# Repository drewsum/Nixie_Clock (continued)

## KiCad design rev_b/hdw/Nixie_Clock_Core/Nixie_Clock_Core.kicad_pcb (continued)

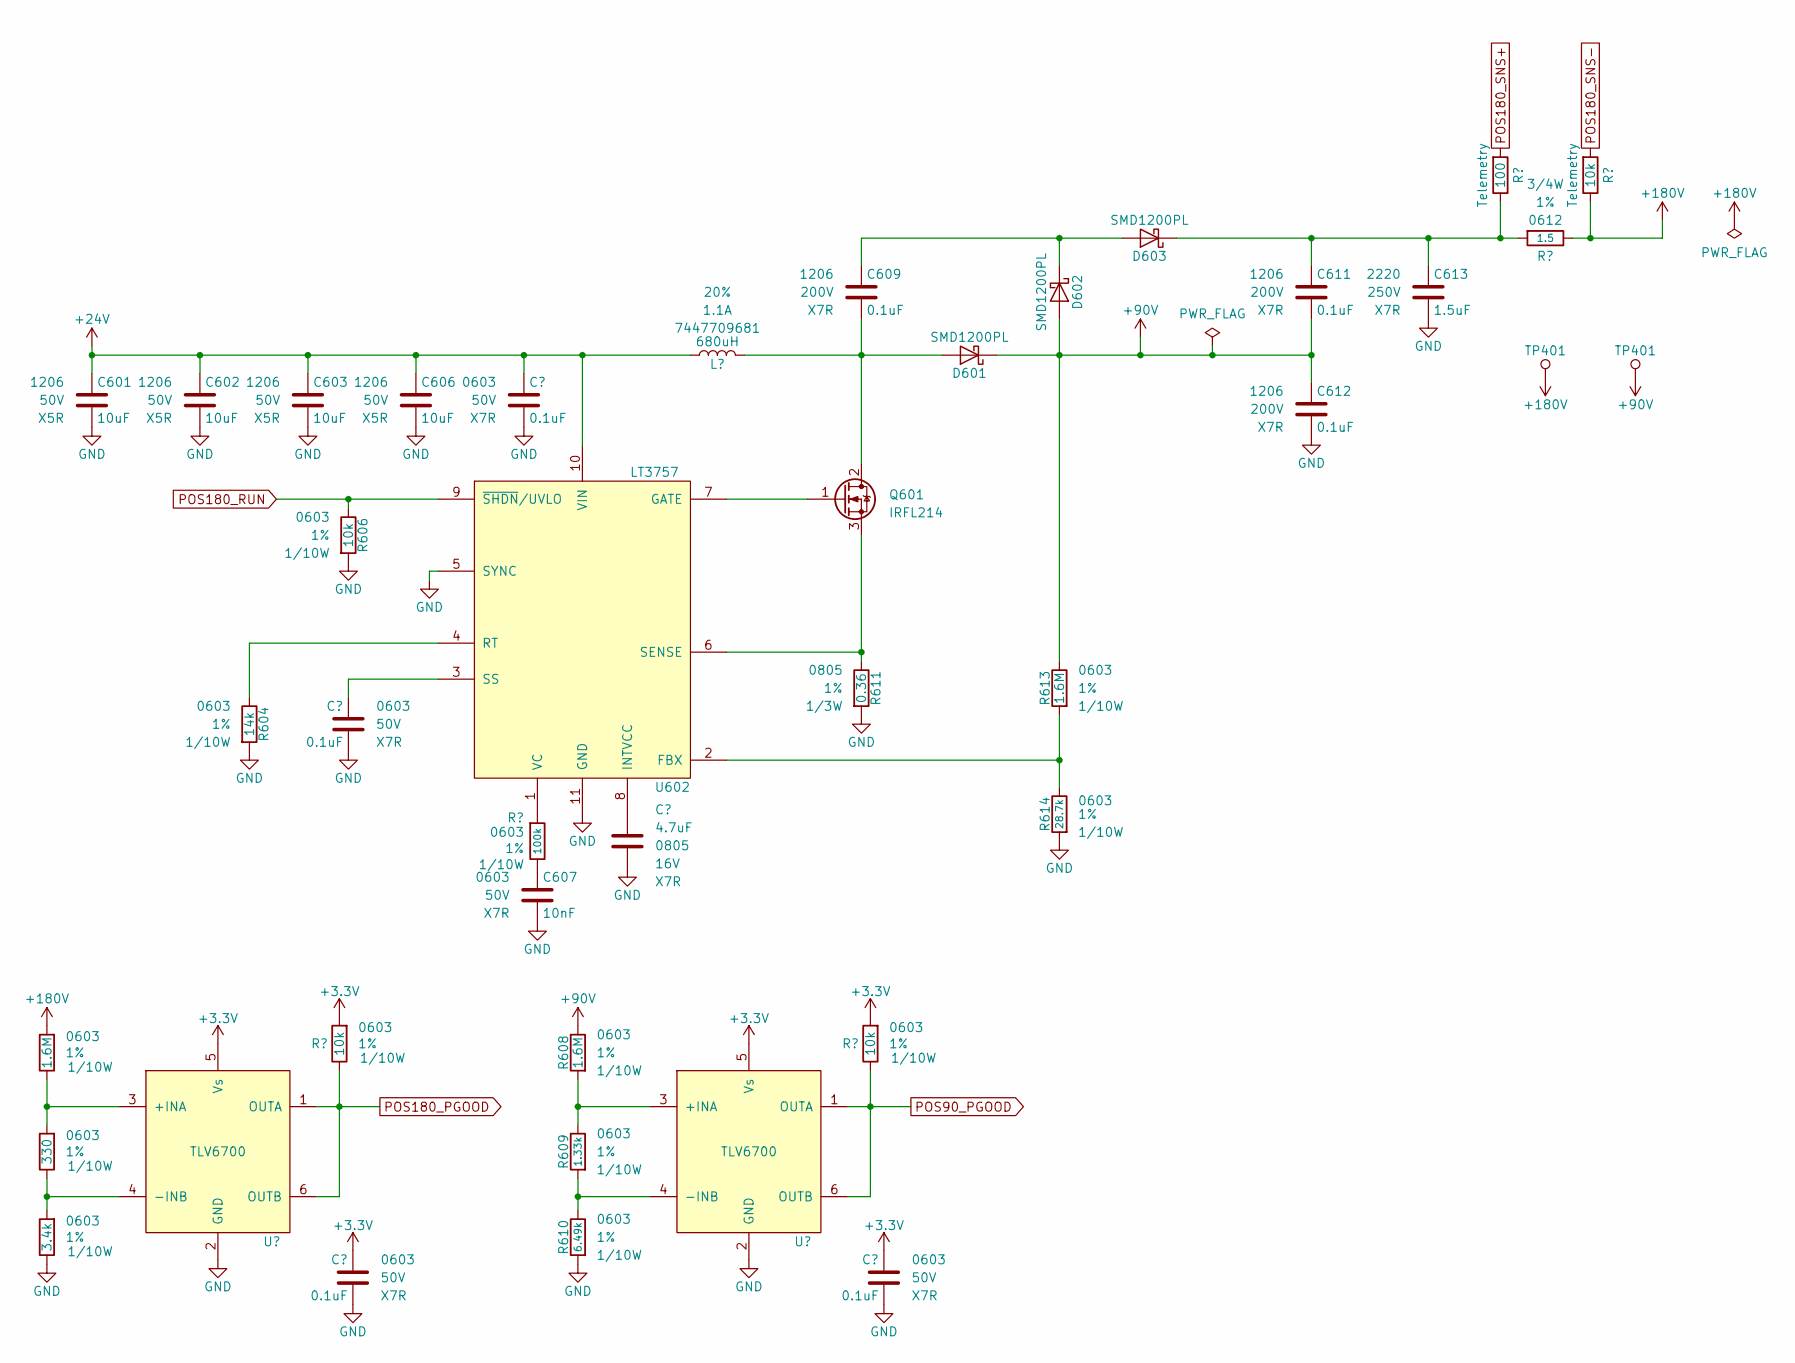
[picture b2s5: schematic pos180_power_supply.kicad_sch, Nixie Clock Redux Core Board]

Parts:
C601, C602, C603, C606: 10uF; C_1206; Voltage 50V; Digi-Key PN 1276-6767-1-ND
C604, C605, C610, C614: 0.1uF; C_0603; Voltage 50V; Digi-Key PN 1276-1935-1-ND
C607: 10nF; C_0603; Voltage 50V; Digi-Key PN 1276-1009-1-ND
C608: 4.7uF; C_0805; Voltage 16V; Digi-Key PN 1276-2970-1-ND
C609, C611, C612: 0.1uF; C_1206; Voltage 200V; Digi-Key PN 399-C1206C104K2RECAUTOCT-ND
C613: 1.5uF; C_2220; Voltage 250V; Digi-Key PN 565-4697-1-ND
D601, D602, D603: SMD1200PL; D_SOD-123F; Digi-Key PN SMD1200PL-TPMSCT-ND
L601: 680uH; Wurth_7447709681; Tolerance 20%; Digi-Key PN 732-1700-1-ND
Q601: IRFL214; SOT-223-3_TabPin2; Digi-Key PN IRFL214PBFCT-ND
R601, R608, R613: 1.6M; R_0603; Tolerance 1%; Digi-Key PN 541-1.60MHCT-ND
R602: 330; R_0603; Tolerance 1%; Digi-Key PN 541-330HCT-ND
R603: 3.4k; R_0603; Tolerance 1%; Digi-Key PN 541-3.40KHCT-ND
R604: 14k; R_0603; Tolerance 1%; Digi-Key PN 541-CRCW060314K0FKTACT-ND
R605, R606, R612, R617: 10k; R_0603; Tolerance 1%; Digi-Key PN 541-10.0KHCT-ND
R607: 100k; R_0603; Tolerance 1%; Digi-Key PN 541-100KHCT-ND
R609: 1.33k; R_0603; Tolerance 1%; Digi-Key PN 541-1.33KHCT-ND
R610: 6.49k; R_0603; Tolerance 1%; Digi-Key PN 541-5537-1-ND
R611: 0.36; R_0805; Tolerance 1%; Digi-Key PN RL12S.36FCT-ND
R614: 28.7k; R_0603; Tolerance 1%; Digi-Key PN 541-28.7KHCT-ND
R615: 100; R_0603; Tolerance 1%; Digi-Key PN 541-3951-1-ND
R616: 1.5; R_0612; Tolerance 1%; Digi-Key PN RCL06121R20FKEA
TP401: TP; Test_Point
U601, U603: TLV6700; SOT-23-6; Digi-Key PN 296-51696-1-ND
U602: LT3757; DFN-10-1EP_3x3mm_Pitch0.5mm; Digi-Key PN LT3757IDD#PBF

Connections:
+24V: C601.1, C602.1, C603.1, C606.1, C614.1, L601.1, U602.10 (VIN); also elsewhere on the board
GND: C601.2, C602.2, C603.2, C604.2, C605.2, C606.2, C607.2, C608.2, C610.2, C612.2, C613.2, C614.2, R603.2, R604.2, R606.2, R610.2, R611.2, R614.2, U601.2 (GND), U602.5 (SYNC), U602.11 (GND), U603.2 (GND); also elsewhere on the board
unnamed: C607.1, R607.2
unnamed: C609.2, D601.2 (A), L601.2, Q601.2 (D)
unnamed: C609.1, D602.1 (K), D603.2 (A)
unnamed: C611.1, C613.1, D603.1 (K), R615.2, R616.1
unnamed: Q601.1 (G), U602.7 (GATE)
unnamed: Q601.3 (S), R611.1, U602.6 (SENSE)
unnamed: R601.2, R602.1, U601.3 (+INA)
unnamed: R602.2, R603.1, U601.4 (-INB)
unnamed: R613.2, R614.1, U602.2 (FBX)
unnamed: C608.1, U602.8 (INTVCC)
unnamed: R604.1, U602.4 (RT)
unnamed: C604.1, U602.3 (SS)
unnamed: R607.1, U602.1 (VC)
unnamed: R608.2, R609.1, U603.3 (+INA)
unnamed: R609.2, R610.1, U603.4 (-INB)
POS90_PGOOD: R612.2, U603.1 (OUTA), U603.6 (OUTB); also elsewhere on the board
POS180_PGOOD: R605.2, U601.1 (OUTA), U601.6 (OUTB); also elsewhere on the board
POS180_RUN: R606.1, U602.9 (~SHDN/UVLO); also elsewhere on the board
POS180_SNS+: R615.1; also elsewhere on the board
POS180_SNS-: R617.1; also elsewhere on the board

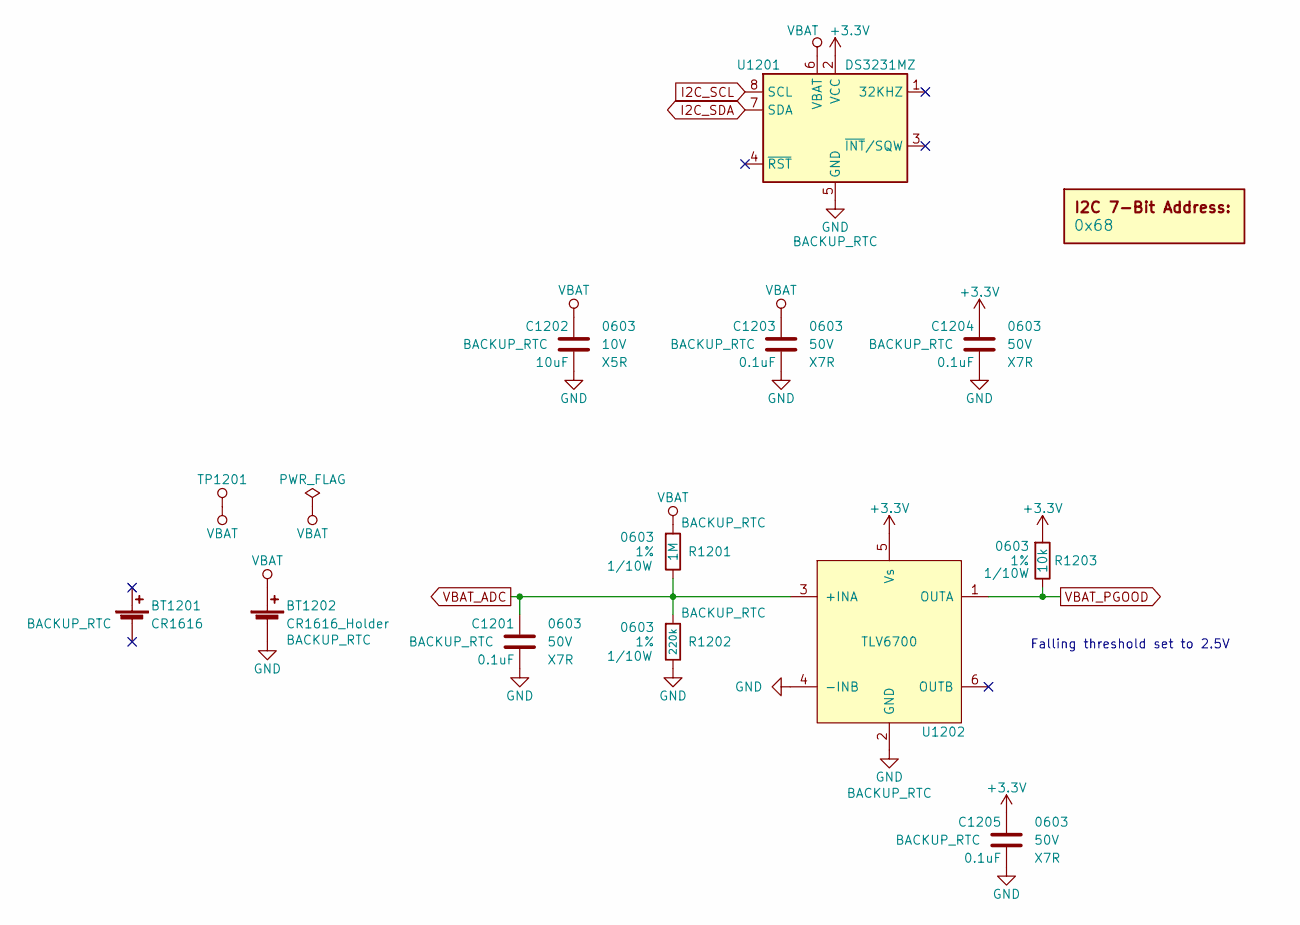
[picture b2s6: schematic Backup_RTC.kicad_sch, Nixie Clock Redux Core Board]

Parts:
BT1201: CR1616; Digi-Key PN P034-ND
BT1202: CR1616_Holder; BAT_BU1632SM-JJ-GTR; Digi-Key PN BU1632SM-JJ-GCT-ND
C1201, C1203, C1204, C1205: 0.1uF; C_0603; Voltage 50V; Digi-Key PN 1276-1935-1-ND
C1202: 10uF; C_0603; Voltage 10V; Digi-Key PN 1276-1871-1-ND
DOC1201: 0x68
R1201: 1M; R_0603; Tolerance 1%; Digi-Key PN 541-1.00MHCT-ND
R1202: 220k; R_0603; Tolerance 1%; Digi-Key PN 541-4039-1-ND
R1203: 10k; R_0603; Tolerance 1%; Digi-Key PN 541-10.0KHCT-ND
TP1201: TP; Test_Point
U1201: DS3231MZ; SOIC-8_3.9x4.9mm_P1.27mm; Digi-Key PN DS3231MZ+-ND
U1202: TLV6700; SOT-23-6; Digi-Key PN 296-51696-1-ND

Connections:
GND: BT1202.2 (-), C1201.2, C1202.2, C1203.2, C1204.2, C1205.2, R1202.2, U1201.5 (GND), U1202.2 (GND), U1202.4 (-INB); also elsewhere on the board
I2C_SCL: U1201.8 (SCL); also elsewhere on the board
I2C_SDA: U1201.7 (SDA); also elsewhere on the board
VBAT: BT1202.1 (+), C1202.1, C1203.1, R1201.1, TP1201.1 (TP), U1201.6 (VBAT)
VBAT_ADC: C1201.1, R1201.2, R1202.1, U1202.3 (+INA); also elsewhere on the board
VBAT_PGOOD: R1203.2, U1202.1 (OUTA); also elsewhere on the board

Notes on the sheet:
Falling threshold set to 2.5V

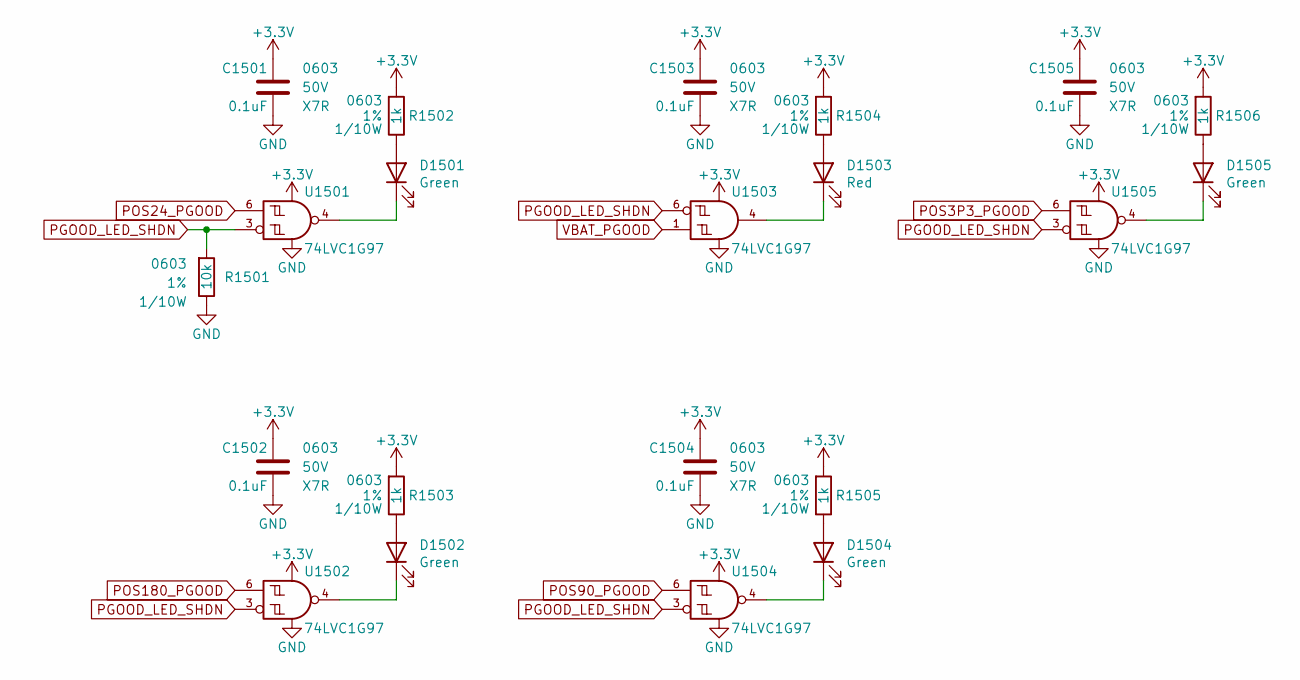
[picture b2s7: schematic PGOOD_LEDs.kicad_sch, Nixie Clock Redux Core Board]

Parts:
C1501, C1502, C1503, C1504, C1505: 0.1uF; C_0603; Voltage 50V; Digi-Key PN 1276-1935-1-ND
D1501, D1502, D1504, D1505: Green; LED_0603; Digi-Key PN 754-1121-1-ND
D1503: Red; LED_0603; Digi-Key PN 754-1117-1-ND
R1501: 10k; R_0603; Tolerance 1%; Digi-Key PN 541-10.0KHCT-ND
R1502, R1503, R1504, R1505, R1506: 1k; R_0603; Tolerance 1%; Digi-Key PN 541-1.00KHCT-ND
U1501, U1502, U1503, U1504, U1505: 74LVC1G97; SOT-363_SC-70-6; Digi-Key PN 296-15582-1-ND

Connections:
GND: C1501.2, C1502.2, C1503.2, C1504.2, C1505.2, R1501.2, U1501.2 (GND), U1502.2 (GND), U1503.2 (GND), U1503.3 (GND), U1504.2 (GND), U1505.2 (GND); also elsewhere on the board
unnamed: D1501.2 (A), R1502.2
unnamed: D1501.1 (K), U1501.4
unnamed: D1502.2 (A), R1503.2
unnamed: D1502.1 (K), U1502.4
unnamed: D1503.2 (A), R1504.2
unnamed: D1503.1 (K), U1503.4
unnamed: D1504.2 (A), R1505.2
unnamed: D1504.1 (K), U1504.4
unnamed: D1505.2 (A), R1506.2
unnamed: D1505.1 (K), U1505.4
PGOOD_LED_SHDN: R1501.1, U1501.3, U1502.3, U1503.6, U1504.3, U1505.3; also elsewhere on the board
POS3P3_PGOOD: U1505.6; also elsewhere on the board
POS24_PGOOD: U1501.6; also elsewhere on the board
POS90_PGOOD: U1504.6; also elsewhere on the board
POS180_PGOOD: U1502.6; also elsewhere on the board
VBAT_PGOOD: U1503.1; also elsewhere on the board

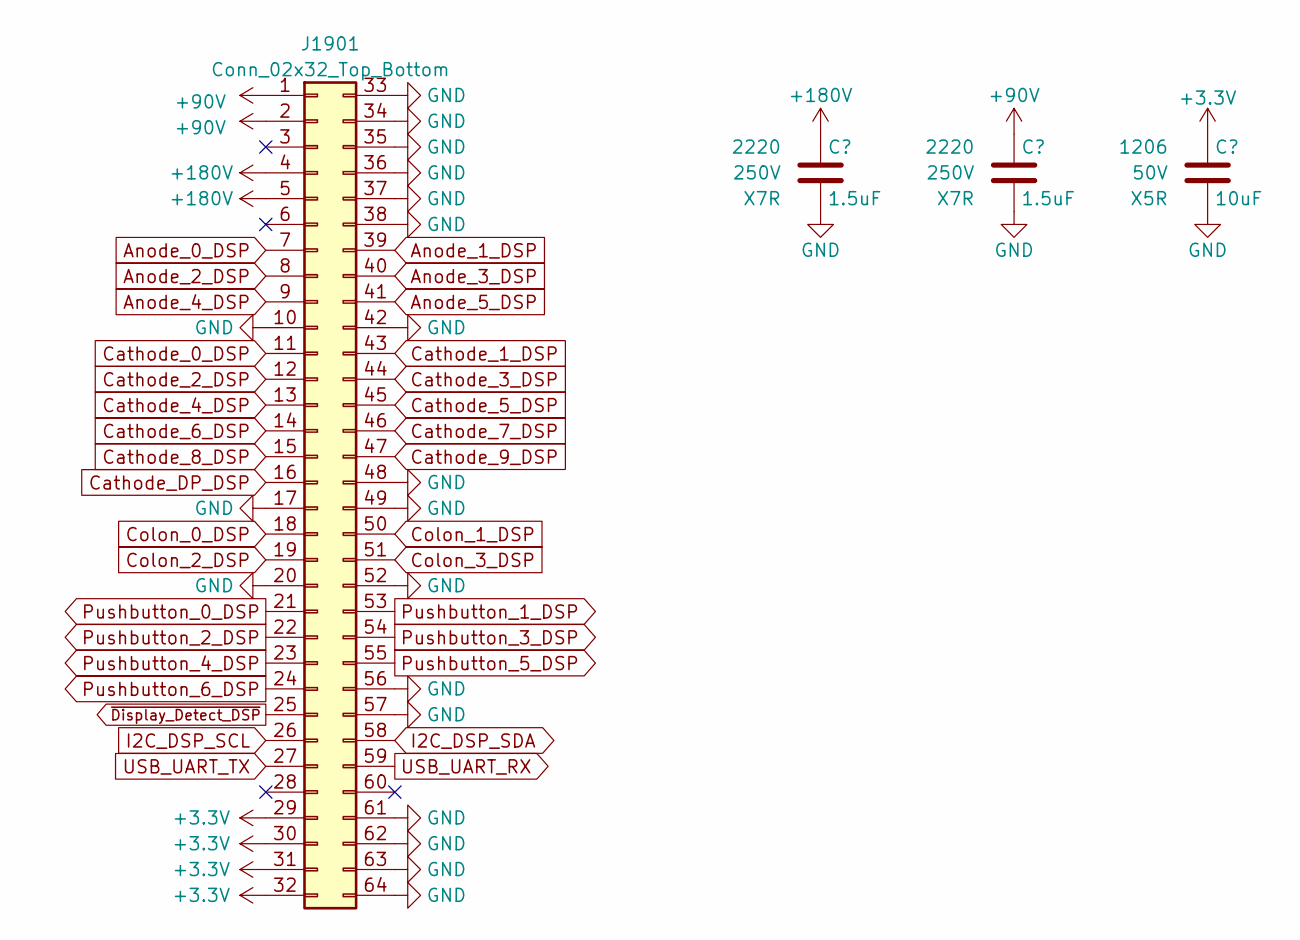
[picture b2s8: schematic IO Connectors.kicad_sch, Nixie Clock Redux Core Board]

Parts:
C1901, C1902: 1.5uF; C_2220; Voltage 250V; Digi-Key PN 565-4697-1-ND
C1903: 10uF; C_1206; Voltage 50V; Digi-Key PN 1276-6767-1-ND
J1901: Conn_02x32_Top_Bottom; CONN_5120527-1_TYC; Digi-Key PN A97407CT-ND

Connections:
Anode_0_DSP: J1901.7; also elsewhere on the board
Anode_1_DSP: J1901.39; also elsewhere on the board
Anode_2_DSP: J1901.8; also elsewhere on the board
Anode_3_DSP: J1901.40; also elsewhere on the board
Anode_4_DSP: J1901.9; also elsewhere on the board
Anode_5_DSP: J1901.41; also elsewhere on the board
Cathode_0_DSP: J1901.11; also elsewhere on the board
Cathode_1_DSP: J1901.43; also elsewhere on the board
Cathode_2_DSP: J1901.12; also elsewhere on the board
Cathode_3_DSP: J1901.44; also elsewhere on the board
Cathode_4_DSP: J1901.13; also elsewhere on the board
Cathode_5_DSP: J1901.45; also elsewhere on the board
Cathode_6_DSP: J1901.14; also elsewhere on the board
Cathode_7_DSP: J1901.46; also elsewhere on the board
Cathode_8_DSP: J1901.15; also elsewhere on the board
Cathode_9_DSP: J1901.47; also elsewhere on the board
Cathode_DP_DSP: J1901.16; also elsewhere on the board
Colon_0_DSP: J1901.18; also elsewhere on the board
Colon_1_DSP: J1901.50; also elsewhere on the board
Colon_2_DSP: J1901.19; also elsewhere on the board
Colon_3_DSP: J1901.51; also elsewhere on the board
GND: C1901.2, C1902.2, C1903.2, J1901.10, J1901.17, J1901.20, J1901.33, J1901.34, J1901.35, J1901.36, J1901.37, J1901.38, J1901.42, J1901.48, J1901.49, J1901.52, J1901.56, J1901.57, J1901.61, J1901.62, J1901.63, J1901.64; also elsewhere on the board
I2C_DSP_SCL: J1901.26; also elsewhere on the board
I2C_DSP_SDA: J1901.58; also elsewhere on the board
Pushbutton_0_DSP: J1901.21; also elsewhere on the board
Pushbutton_1_DSP: J1901.53; also elsewhere on the board
Pushbutton_2_DSP: J1901.22; also elsewhere on the board
Pushbutton_3_DSP: J1901.54; also elsewhere on the board
Pushbutton_4_DSP: J1901.23; also elsewhere on the board
Pushbutton_5_DSP: J1901.55; also elsewhere on the board
Pushbutton_6_DSP: J1901.24; also elsewhere on the board
USB_UART_RX: J1901.59; also elsewhere on the board
USB_UART_TX: J1901.27; also elsewhere on the board
~Display_Detect_DSP: J1901.25; also elsewhere on the board

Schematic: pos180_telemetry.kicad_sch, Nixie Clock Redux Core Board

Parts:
C701, C702, C703, C704, C705, C706, C707, C708, C709, C710: 0.1uF; C_0603; Voltage 50V; Digi-Key PN 1276-1935-1-ND
D701: BZX58550-C5V1X; D_SOD-523; Digi-Key PN 1727-BZX58550-C5V1XCT-ND
DOC701: 0x20
DOC702: 0x42
Q701: BSS192PH6327FTSA1; SOT-89-3; Digi-Key PN BSS192PH6327FTSA1CT-ND
R701: 2M; R_0603; Tolerance 1%; Digi-Key PN 541-5333-1-ND
R702: 100; R_0603; Tolerance 1%; Digi-Key PN 541-3951-1-ND
R703: 150k; R_0603; Tolerance 1%; Digi-Key PN 541-CRCW0603150KFKTACT-ND
R704, R706, R707, R708: 1k; R_0603; Tolerance 1%; Digi-Key PN 541-1.00KHCT-ND
R705: 75k; R_0603; Tolerance 1%; Digi-Key PN 541-5552-1-ND
U701, U704, U705: OPA333xxDCK; SOT-353_SC-70-5; Digi-Key PN 296-22188-1-ND
U702: MCP9804; DFN-8-1EP_3x2mm_P0.5mm_EP1.3x1.5mm; Digi-Key PN MCP9804T-E/MCCT-ND
U703: INA219BxDCN; SOT-23-8; Digi-Key PN 296-46420-1-ND

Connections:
GND: C701.2, C703.2, C704.2, C705.2, C706.2, C707.2, C708.2, C709.2, C710.2, R701.2, R702.2, R704.2, R706.2, U702.4 (GND), U702.5 (A2), U702.7 (A0), U702.9 (EP/GND), U703.2 (IN-), U703.3 (GND), U703.7 (A0), U704.2 (V-), U705.2 (V-); also elsewhere on the board
I2C_SCL: U702.2 (SCL), U703.5 (SCL); also elsewhere on the board
I2C_SDA: U702.1 (SDA), U703.6 (SDA); also elsewhere on the board
unnamed: C702.2, D701.2 (A), R701.1, U701.2 (V-)
unnamed: C703.1, Q701.2 (D), R702.1, U703.1 (IN+)
unnamed: Q701.1 (G), U701.4
unnamed: C705.1, R703.2, R704.1, U704.1 (+)
unnamed: R707.1, U704.3 (-), U704.4
unnamed: C706.1, R705.2, R706.1, U705.1 (+)
unnamed: R708.1, U705.3 (-), U705.4
POS90_ADC: C708.1, R708.2; also elsewhere on the board
POS180_ADC: C707.1, R707.2; also elsewhere on the board
POS180_SNS+: Q701.3 (S), U701.3 (-); also elsewhere on the board
POS180_SNS-: U701.1 (+); also elsewhere on the board

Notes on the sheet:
POS180 ADC gain = 151 POS90 ADC gain = 76
RSHUNT = 1.5 CLSB = 0.8uA
From TIDU849
Shunt = 1.5 Ohm R_mon = 100 Ohm POS180 Load = 30mA I_FET ~ 450uA V_mon = 45mV P_FET ~ 80mW

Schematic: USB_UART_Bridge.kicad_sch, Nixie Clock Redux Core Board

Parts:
C1301, C1302, C1303, C1305, C1306, C1307, C1310, C1312: 0.1uF; C_0603; Voltage 50V; Digi-Key PN 1276-1935-1-ND
C1304, C1311, C1313: 10uF; C_0603; Voltage 10V; Digi-Key PN 1276-1871-1-ND
C1308, C1309: 47pF; C_0603; Voltage 50V; Digi-Key PN 13-CC0603JPNPO9BN470CT-ND
D1301: Yellow; LED_0603; Digi-Key PN 754-1124-1-ND
D1302: Green; LED_0603; Digi-Key PN 754-1121-1-ND
DOC1301: COM_Port_Settings
J1301: USB_B_Mini; USB_Mini-B; Digi-Key PN 732-2109-1-ND
L1301, L1302: 600R 0.5A; L_0603; Digi-Key PN 490-1014-1-ND
R1301, R1310: 1k; R_0603; Tolerance 1%; Digi-Key PN 541-1.00KHCT-ND
R1302: 487k; R_0603; Tolerance 1%; Digi-Key PN 541-487KHCT-ND
R1303: 6.04k; R_0603; Tolerance 1%; Digi-Key PN 541-CRCW06036K04FKEBCT-ND
R1304: 40.2k; R_0603; Tolerance 1%; Digi-Key PN 541-5412-1-ND
R1305: 10k; R_0603; Tolerance 1%; Digi-Key PN 541-10.0KHCT-ND
R1306, R1307, R1311, R1312: 100k; R_0603; Tolerance 1%; Digi-Key PN 541-100KHCT-ND
R1308, R1309: 27; R_0603; Tolerance 1%; Digi-Key PN 541-5306-1-ND
TP1301: TP; Test_Point
U1301: TLV6700; SOT-23-6; Digi-Key PN 296-51696-1-ND
U1302: FT234XD; DFN-12-1EP_3x3mm_Pitch0.45mm; Digi-Key PN 768-1178-1-ND
U1303: 74LVC1G97; SOT-363_SC-70-6; Digi-Key PN 296-15582-1-ND
U1304: ISO7321C; SOIC-8_3.9x4.9mm_P1.27mm; Digi-Key PN 296-42102-1-ND
U1305: TPD3S014DBVR; SOT-23-6; Digi-Key PN 296-38835-1-ND

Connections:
+3.3V_USB: C1301.1, C1303.1, C1305.1, C1306.1, C1312.1, C1313.1, R1305.1, R1310.1, R1311.1, R1312.1, U1301.5 (Vs), U1302.3 (3V3OUT), U1302.9 (VCCIO), U1303.1 (VCC), U1303.5 (VCC), U1304.8 (VCC2)
+5V_USB: C1302.1, C1304.1, C1307.1, R1301.1, R1302.1, TP1301.1 (TP), U1302.4 (VCC), U1305.4 (OUT)
/USB UART Bridge/BRIDGE_USB+: R1308.2, U1302.12 (USBDP)
/USB UART Bridge/BRIDGE_USB-: R1309.2, U1302.1 (USBDM)
/USB UART Bridge/CONN_USB+: C1308.1, J1301.3 (D+), R1308.1, U1305.6 (D1)
/USB UART Bridge/CONN_USB-: C1309.1, J1301.2 (D-), R1309.1, U1305.5 (D2)
GND: C1310.2, C1311.2, U1304.4 (GND1); also elsewhere on the board
GND_USB: C1301.2, C1302.2, C1303.2, C1304.2, C1305.2, C1306.2, C1307.2, C1308.2, C1309.2, C1312.2, C1313.2, J1301.5 (GND), L1302.1, R1304.2, U1301.2 (GND), U1302.5 (GND), U1302.13 (GND), U1303.2 (GND), U1303.3 (GND), U1304.5 (GND2), U1305.2 (GND)
unnamed: D1301.2 (A), R1301.2
unnamed: D1302.2 (A), R1310.2
unnamed: D1302.1 (K), U1303.4
unnamed: J1301.6 (Shield), L1302.2
unnamed: J1301.1 (VBUS), L1301.1
unnamed: R1302.2, R1303.1, U1301.3 (+INA)
unnamed: R1303.2, R1304.1, U1301.4 (-INB)
unnamed: L1301.2, U1305.1 (EN), U1305.3 (IN)
POS5_USB_PGOOD: R1305.2, U1301.1 (OUTA), U1301.6 (OUTB), U1303.6
USB_UART_RX: R1307.2, U1304.2 (OUTA); also elsewhere on the board
USB_UART_RX_ISO: R1311.2, U1302.7 (TXD), U1304.7 (INA)
USB_UART_TX: R1306.2, U1304.3 (INB); also elsewhere on the board
USB_UART_TX_ISO: R1312.2, U1302.10 (RXD), U1304.6 (OUTB)
~USB_ACTIVE: D1301.1 (K), U1302.6 (CBUS0)

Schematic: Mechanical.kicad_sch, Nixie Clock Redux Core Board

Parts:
H2001, H2002, H2003, H2004, H2005, H2006, H2007, H2008: MountingHole; MountingHole_3mm

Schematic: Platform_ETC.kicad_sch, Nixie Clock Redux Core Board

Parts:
C1401, C1402, C1403: 10uF; C_0603; Voltage 10V; Digi-Key PN 1276-1871-1-ND
C1404: 0.1uF; C_0603; Voltage 50V; Digi-Key PN 1276-1935-1-ND
D1401: BAT48JFILM; D_SOD-323; Digi-Key PN 497-5711-1-ND
DOC1401: 0x6B
U1401: DS1683; SOIC-8_3.9x4.9mm_Pitch1.27mm; Digi-Key PN DS1683S+-ND

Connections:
GND: C1401.2, C1402.2, C1403.2, C1404.2, U1401.4 (GND); also elsewhere on the board
I2C_SCL: U1401.5 (SCL); also elsewhere on the board
I2C_SDA: U1401.6 (SDA); also elsewhere on the board
unnamed: C1401.1, C1402.1, C1403.1, C1404.1, D1401.1 (K), U1401.8 (VCC)

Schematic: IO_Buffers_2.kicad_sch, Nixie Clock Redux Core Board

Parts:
C1801, C1802, C1804: 0.1uF; C_0603; Voltage 50V; Digi-Key PN 1276-1935-1-ND
C1803, C1805: 4.7uF; C_0805; Voltage 16V; Digi-Key PN 1276-2970-1-ND
R1801, R1802, R1803, R1805, R1806: 10K; R_0603; Tolerance 1%; Digi-Key PN 541-10.0KHCT-ND
RN1801, RN1802: 10k; R_Array_Convex_8x0602; Tolerance 1%; Digi-Key PN Y1103CT-ND
U1801: TCA9803; VSSOP-8_3.0x3.0mm_P0.65mm; Digi-Key PN 296-47829-1-ND
U1802: 74VHC541; WQFN-20-1EP_2.5x4.5mm_P0.5mm_EP1x2.9mm; Digi-Key PN 1727-7068-1-ND

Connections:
GND: C1801.2, C1802.2, C1803.2, C1804.2, C1805.2, RN1801.1 (R1.1), RN1801.2 (R2.1), RN1801.3 (R3.1), RN1801.4 (R4.1), RN1801.5 (R5.1), RN1801.6 (R6.1), RN1801.7 (R7.1), RN1801.8 (R8.1), RN1802.1 (R1.1), RN1802.2 (R2.1), RN1802.3 (R3.1), RN1802.4 (R4.1), RN1802.5 (R5.1), RN1802.6 (R6.1), RN1802.7 (R7.1), RN1802.8 (R8.1), U1801.4 (GND), U1802.10 (GND), U1802.21 (GND); also elsewhere on the board
I2C_DSP_SCL: R1805.2, U1801.7 (SCLB); also elsewhere on the board
I2C_DSP_SDA: R1803.2, U1801.6 (SDAB); also elsewhere on the board
I2C_SCL: U1801.2 (SCLA); also elsewhere on the board
I2C_SDA: U1801.3 (SDAA); also elsewhere on the board
Pushbutton_0: RN1801.16 (R1.2), U1802.11 (Y7); also elsewhere on the board
Pushbutton_0_DSP: RN1802.9 (R8.2), U1802.9 (A7); also elsewhere on the board
Pushbutton_1: RN1801.15 (R2.2), U1802.12 (Y6); also elsewhere on the board
Pushbutton_1_DSP: RN1802.10 (R7.2), U1802.8 (A6); also elsewhere on the board
Pushbutton_2: RN1801.14 (R3.2), U1802.13 (Y5); also elsewhere on the board
Pushbutton_2_DSP: RN1802.11 (R6.2), U1802.7 (A5); also elsewhere on the board
Pushbutton_3: RN1801.13 (R4.2), U1802.14 (Y4); also elsewhere on the board
Pushbutton_3_DSP: RN1802.12 (R5.2), U1802.6 (A4); also elsewhere on the board
Pushbutton_4: RN1801.12 (R5.2), U1802.15 (Y3); also elsewhere on the board
Pushbutton_4_DSP: RN1802.13 (R4.2), U1802.5 (A3); also elsewhere on the board
Pushbutton_5: RN1801.11 (R6.2), U1802.16 (Y2); also elsewhere on the board
Pushbutton_5_DSP: RN1802.14 (R3.2), U1802.4 (A2); also elsewhere on the board
Pushbutton_6: RN1801.10 (R7.2), U1802.17 (Y1); also elsewhere on the board
Pushbutton_6_DSP: RN1802.15 (R2.2), U1802.3 (A1); also elsewhere on the board
~Display_Detect_DSP: R1806.2, U1802.2 (A0); also elsewhere on the board
~Display_Detect: R1801.2, U1802.18 (Y0); also elsewhere on the board
~IO_Level_Shift_Enable: R1802.2, U1801.5 (EN), U1802.1 (G1), U1802.19 (G2); also elsewhere on the board

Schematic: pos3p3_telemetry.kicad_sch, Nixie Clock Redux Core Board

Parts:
C501, C502, C503: 0.1uF; C_0603; Voltage 50V; Digi-Key PN 1276-1935-1-ND
DOC501: 0x41
DOC502: 0x19
U501: INA219BxDCN; SOT-23-8; Digi-Key PN 296-46420-1-ND
U502: MCP9804; DFN-8-1EP_3x2mm_P0.5mm_EP1.3x1.5mm; Digi-Key PN MCP9804T-E/MCCT-ND

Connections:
GND: C502.2, C503.2, U501.3 (GND), U501.8 (A1), U502.4 (GND), U502.5 (A2), U502.6 (A1), U502.9 (EP/GND); also elsewhere on the board
I2C_SCL: U501.5 (SCL), U502.2 (SCL); also elsewhere on the board
I2C_SDA: U501.6 (SDA), U502.1 (SDA); also elsewhere on the board
POS3P3_SNS+: C501.1, U501.1 (IN+); also elsewhere on the board
POS3P3_SNS-: C501.2, U501.2 (IN-); also elsewhere on the board

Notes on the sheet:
RSHUNT = 0.02 CLSB = 60uA

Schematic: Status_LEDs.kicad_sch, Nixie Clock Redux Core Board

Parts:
C1601, C1602, C1603, C1604: 0.1uF; C_0603; Voltage 50V; Digi-Key PN 1276-1935-1-ND
D1601: Green; LED_0603; Digi-Key PN 754-1121-1-ND
D1602, D1603, D1604: Red; LED_0603; Digi-Key PN 754-1117-1-ND
R1601, R1602, R1605, R1606: 10k; R_0603; Tolerance 1%; Digi-Key PN 541-10.0KHCT-ND
R1603, R1604, R1607, R1608: 1k; R_0603; Tolerance 1%; Digi-Key PN 541-1.00KHCT-ND
U1601, U1602, U1603, U1604: 74LVC1G97; SOT-363_SC-70-6; Digi-Key PN 296-15582-1-ND

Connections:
CPU_Trap_LED: R1606.1, U1604.6; also elsewhere on the board
Error_LED: R1602.1, U1602.6; also elsewhere on the board
GND: C1601.2, C1602.2, C1603.2, C1604.2, R1601.2, R1602.2, R1606.2, U1601.2 (GND), U1601.3 (GND), U1602.2 (GND), U1602.3 (GND), U1603.2 (GND), U1603.3 (GND), U1604.2 (GND), U1604.3 (GND); also elsewhere on the board
Heartbeat_LED: R1601.1, U1601.6; also elsewhere on the board
unnamed: D1601.2 (A), R1603.2
unnamed: D1601.1 (K), U1601.4
unnamed: D1602.2 (A), R1604.2
unnamed: D1602.1 (K), U1602.4
unnamed: D1603.2 (A), R1607.2
unnamed: D1603.1 (K), U1603.4
unnamed: D1604.2 (A), R1608.2
unnamed: D1604.1 (K), U1604.4
Reset_LED: R1605.2, U1603.6; also elsewhere on the board

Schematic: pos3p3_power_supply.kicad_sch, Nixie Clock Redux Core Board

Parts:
C401, C403, C407, C408: 10uF; C_1206; Voltage 50V; Digi-Key PN 1276-6767-1-ND
C402: 4.7uF; C_0805; Voltage 16V; Digi-Key PN 1276-2970-1-ND
C404: 10nF; C_0603; Voltage 50V; Digi-Key PN 1276-1009-1-ND
C405: 10uF; C_0603; Voltage 10V; Digi-Key PN 1276-1871-1-ND
C406: 0.1uF; C_0603; Voltage 50V; Digi-Key PN 1276-1935-1-ND
C409: 47pF; C_0603; Voltage 50V; Digi-Key PN 13-CC0603JPNPO9BN470CT-ND
D401: BAT48JFILM; D_SOD-323; Digi-Key PN 497-5711-1-ND
L401: 2.2uH; L_Vishay_IHLP-2020; Tolerance 20%; Digi-Key PN 541-1268-1-ND
Q401: BSS214NW; SOT-323_SC-70; Digi-Key PN BSS214NWH6327XTSA1CT-ND
Q402: ZXMS6004FFTA; SOT-23; Digi-Key PN ZXMS6004FFCT-ND
R401, R405, R407: 10; R_0603; Tolerance 1%; Digi-Key PN 541-10.0HCT-ND
R402, R404: 10k; R_0603; Tolerance 1%; Digi-Key PN 541-10.0KHCT-ND
R403: 18.2k; R_0603; Tolerance 1%; Digi-Key PN 541-18.2KHCT-ND
R406: 0.02; R_0612; Tolerance 1%; Digi-Key PN P16010CT-ND
R408: 1M; R_0603; Tolerance 1%; Digi-Key PN 541-1.00MHCT-ND
R409: 309k; R_0603; Tolerance 1%; Digi-Key PN 541-309KHCT-ND
TP401: TP; Test_Point
U401: LT8609A-DD; DFN-10-1EP_3x3mm_Pitch0.5mm; Digi-Key PN 505-LT8609AEDDM#TRPBFCT-ND

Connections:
+24V: C401.1, C403.1, U401.9 (VIN); also elsewhere on the board
GND: C401.2, C402.2, C403.2, C404.2, C405.2, C407.2, C408.2, Q401.2 (S), Q402.2 (S), R403.2, R409.2, U401.11 (GND); also elsewhere on the board
unnamed: C407.1, C408.1, L401.2, R405.2, R406.1
unnamed: C405.1, D401.1 (K), R404.1
unnamed: Q401.3 (D), Q402.1 (G), R404.2
unnamed: C406.1, U401.1 (BST)
unnamed: C409.2, R408.2, R409.1, U401.6 (FB)
unnamed: C402.1, U401.3 (INTVCC), U401.5 (SYNC)
unnamed: R403.1, U401.4 (RT)
unnamed: C406.2, L401.1, U401.2 (SW)
unnamed: C404.1, U401.7 (TR/SS)
POS3P3_PGOOD: R402.2, U401.8 (PG); also elsewhere on the board
POS3P3_RUN: Q401.1 (G), R401.2, U401.10 (EN/UV)
POS3P3_SNS+: R405.1; also elsewhere on the board
POS3P3_SNS-: R407.1; also elsewhere on the board
POS24_PGOOD: R401.1; also elsewhere on the board

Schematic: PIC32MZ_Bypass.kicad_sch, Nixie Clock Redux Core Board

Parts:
C901, C902, C905, C906, C909, C910, C913, C914: 0.1uF; C_0603; Voltage 50V; Digi-Key PN 1276-1935-1-ND
C903, C904, C907, C908, C911, C912, C915, C916: 10uF; C_0603; Voltage 10V; Digi-Key PN 1276-1871-1-ND
L901, L902: 600R 0.5A; L_0603; Digi-Key PN 490-1014-1-ND

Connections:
+3.3VA_MZ: C914.1, C916.1, L901.1; also elsewhere on the board
GND: C901.2, C902.2, C903.2, C904.2, C905.2, C906.2, C907.2, C908.2, C909.2, C910.2, C911.2, C912.2, C913.2, C915.2, L902.2; also elsewhere on the board
GNDA_MZ: C914.2, C916.2, L902.1; also elsewhere on the board

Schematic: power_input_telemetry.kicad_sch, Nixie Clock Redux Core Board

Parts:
C301, C302, C303: 0.1uF; C_0603; Voltage 50V; Digi-Key PN 1276-1935-1-ND
DOC301: 0x40
DOC302: 0x18
U301: INA219BxDCN; SOT-23-8; Digi-Key PN 296-46420-1-ND
U302: MCP9804; DFN-8-1EP_3x2mm_P0.5mm_EP1.3x1.5mm; Digi-Key PN MCP9804T-E/MCCT-ND

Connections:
GND: C302.2, C303.2, U301.3 (GND), U301.7 (A0), U301.8 (A1), U302.4 (GND), U302.5 (A2), U302.6 (A1), U302.7 (A0), U302.9 (EP/GND); also elsewhere on the board
I2C_SCL: U301.5 (SCL), U302.2 (SCL); also elsewhere on the board
I2C_SDA: U301.6 (SDA), U302.1 (SDA); also elsewhere on the board
POS24_SNS+: C301.1, U301.1 (IN+); also elsewhere on the board
POS24_SNS-: C301.2, U301.2 (IN-); also elsewhere on the board

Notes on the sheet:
RSHUNT = 0.02 CLSB = 60uA

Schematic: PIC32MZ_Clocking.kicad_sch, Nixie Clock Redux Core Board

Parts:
C1101, C1102, C1103: 0.1uF; C_0603; Voltage 50V; Digi-Key PN 1276-1935-1-ND
C1104, C1105: 10uF; C_0603; Voltage 10V; Digi-Key PN 1276-1871-1-ND
L1101, L1102: 600R 0.5A; L_0603; Digi-Key PN 490-1014-1-ND
R1101, R1102, R1105, R1106: 10k; R_0603; Tolerance 1%; Digi-Key PN 541-10.0KHCT-ND
R1103, R1104: 10; R_0603; Tolerance 1%; Digi-Key PN 541-10.0HCT-ND
TP1101: TP; Test_Point
U1101: 74LVC1G97; SOT-363_SC-70-6; Digi-Key PN 296-15582-1-ND
X1101: ASE-8.000MHz; Oscillator_SMD_Abracon_ASE-4Pin_3.2x2.5mm; Digi-Key PN 535-9558-1-ND
X1102: ECS-327KE; Digi-Key PN XC1751CT-ND

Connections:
GND: C1101.2, C1102.2, C1103.2, C1104.2, C1105.2, R1101.2, R1102.2, R1105.2, R1106.2, U1101.2 (GND), U1101.3 (GND), U1101.6 (GND), X1101.2 (GND), X1102.2 (GND); also elsewhere on the board
unnamed: R1103.1, R1105.1, X1101.3 (OUT)
unnamed: C1102.1, C1104.1, L1101.1, X1101.4 (Vdd)
unnamed: R1104.1, R1106.1, X1102.3 (OUT)
unnamed: C1103.1, C1105.1, L1102.1, X1102.4 (Vdd)
PIC32MZ_CLK_EN: R1102.1, U1101.4, X1101.1 (EN), X1102.1 (EN)
PIC32MZ_POSC_EC: R1103.2; also elsewhere on the board
PIC32MZ_REFCLK1: R1101.1, TP1101.1 (TP); also elsewhere on the board
PIC32MZ_SOSC_EC: R1104.2; also elsewhere on the board
POS3P3_PGOOD: U1101.1; also elsewhere on the board

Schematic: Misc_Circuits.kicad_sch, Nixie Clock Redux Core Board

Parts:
BZ2101: CST-931RP-A; MagneticBuzzer_CUI_CST-931RP-A; Digi-Key PN 102-1461-ND
C2101, C2102, C2103: 0.1uF; C_0603; Voltage 50V; Digi-Key PN 1276-1935-1-ND
D2101: SMD1200PL; D_SOD-123F; Digi-Key PN SMD1200PL-TPMSCT-ND
DOC2101: 0x1C
J2101: I2C; PinHeader_1x03_P2.54mm_Vertical
J2102: USB UART; PinHeader_1x03_P2.54mm_Vertical
Q2101: BSS214NW; SOT-323_SC-70; Digi-Key PN BSS214NWH6327XTSA1CT-ND
R2101: 1.07M; R_0603; Tolerance 1%; Digi-Key PN 541-1.07MHCT-ND
R2102, R2104, R2105, R2107, R2108, R2111: 10k; R_0603; Tolerance 1%; Digi-Key PN 541-10.0KHCT-ND
R2103, R2106, R2109, R2110: 10; R_0603; Tolerance 1%; Digi-Key PN 541-10.0HCT-ND
U2101: LTC6900; SOT-23-5; Digi-Key PN LTC6900CS5#TRMPBFCT-ND
U2102: 74LVC1G97; SOT-363_SC-70-6; Digi-Key PN 296-15582-1-ND
U2103: MCP9804; DFN-8-1EP_3x2mm_P0.5mm_EP1.3x1.5mm; Digi-Key PN MCP9804T-E/MCCT-ND

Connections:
Buzzer_Enable: R2107.2, U2102.3; also elsewhere on the board
ETC_Hardstrap: R2105.2, R2106.1; also elsewhere on the board
GND: C2101.2, C2102.2, C2103.2, J2101.3, J2102.3, Q2101.2 (S), R2103.2, R2104.1, R2106.2, R2107.1, R2109.2, R2111.1, U2101.2 (GND), U2102.1 (GND), U2102.2 (GND), U2103.4 (GND), U2103.6 (A1), U2103.7 (A0), U2103.9 (EP/GND); also elsewhere on the board
I2C_SCL: J2101.1, U2103.2 (SCL); also elsewhere on the board
I2C_SDA: J2101.2, U2103.1 (SDA); also elsewhere on the board
unnamed: BZ2101.2 (+), D2101.2 (A), Q2101.3 (D)
unnamed: Q2101.1 (G), R2110.1, R2111.2
unnamed: R2110.2, U2102.4
unnamed: R2104.2, U2101.5 (OUT), U2102.6
unnamed: R2101.2, U2101.3 (SET)
RTC_Hardstrap: R2108.2, R2109.1; also elsewhere on the board
Telemetry_Hardstrap: R2102.2, R2103.1; also elsewhere on the board
USB_UART_RX: J2102.2; also elsewhere on the board
USB_UART_TX: J2102.1; also elsewhere on the board

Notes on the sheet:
Fosc ~ 2kHz
Place away from power components
